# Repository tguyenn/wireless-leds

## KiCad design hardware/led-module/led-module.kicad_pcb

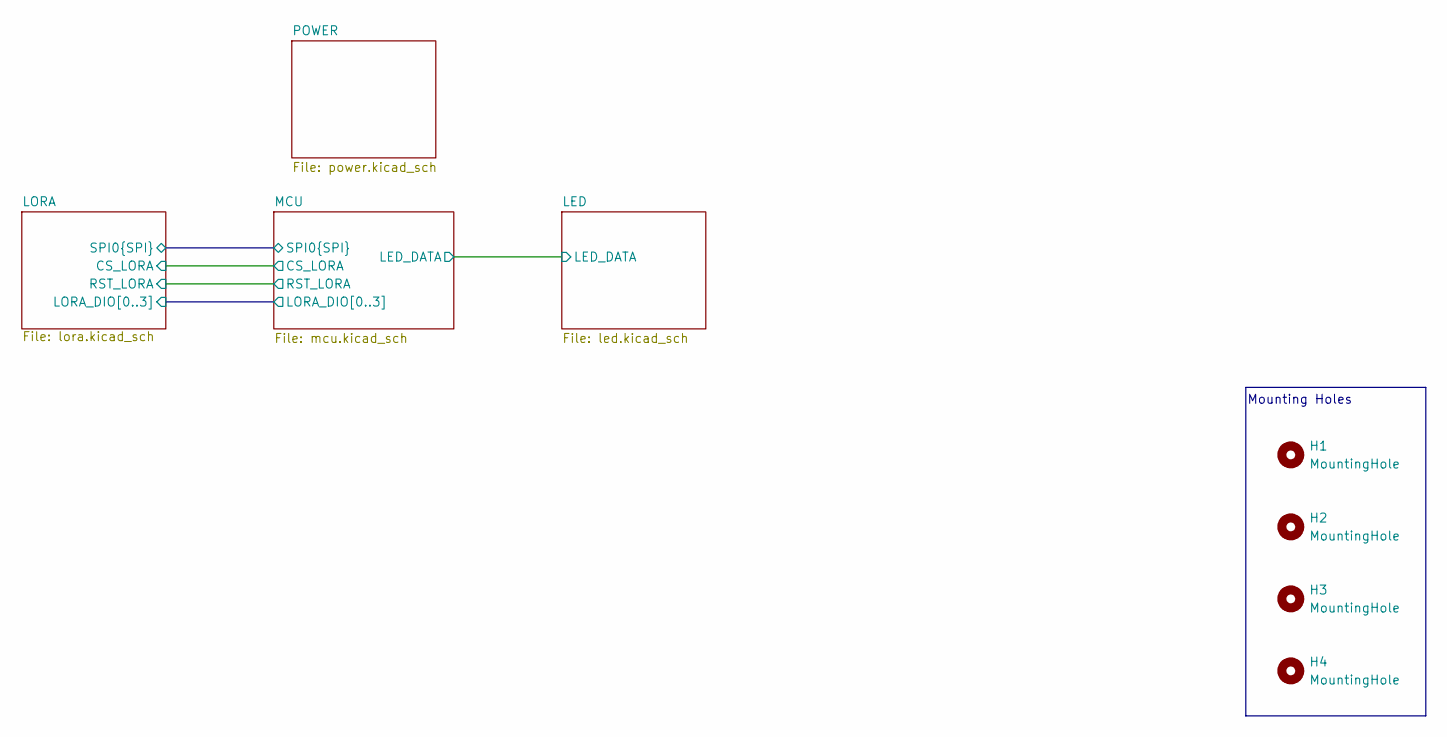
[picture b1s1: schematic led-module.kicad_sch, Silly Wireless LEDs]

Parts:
H1, H2, H3, H4: MountingHole; MountingHole_3mm

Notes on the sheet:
Mounting Holes

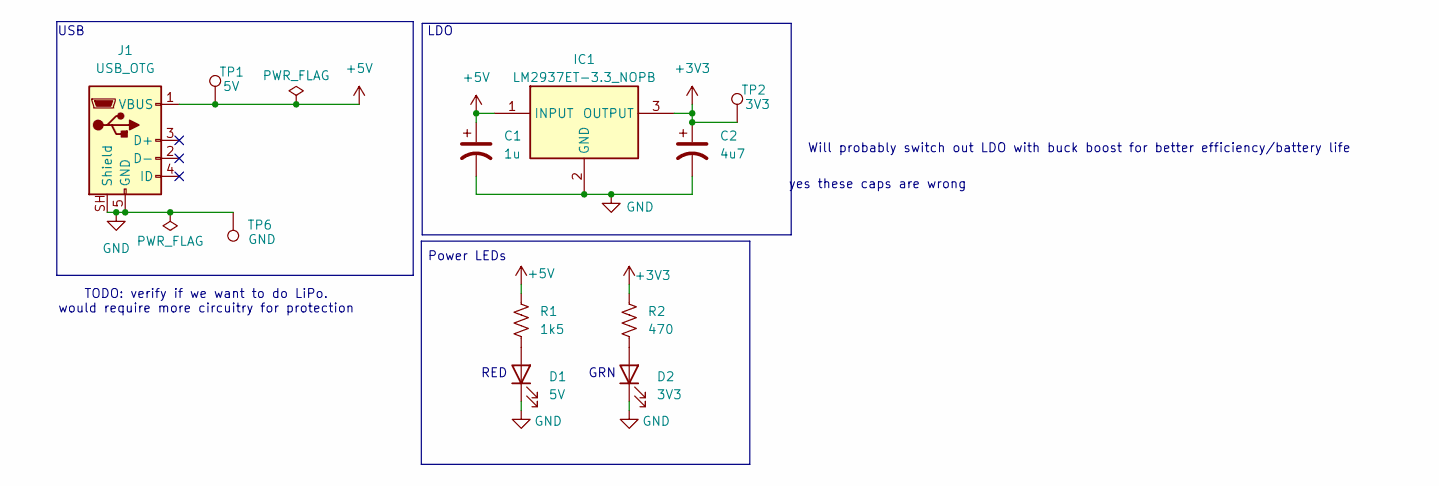
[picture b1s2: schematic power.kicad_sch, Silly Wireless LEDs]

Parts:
C1: 1u; C_0805_2012Metric
C2: 4u7; C_0805_2012Metric
D1: 5V; fuckassled
D2: 3V3; fuckassled
IC1: LM2937ET-3.3_NOPB; TO254P470X1028X1955-3P; Mouser Part Number 926-LM2937ET-3.3NOPB
J1: USB_OTG; USB_Micro-B_GCT_USB3076-30-A
R1: 1k5; R_0805_2012Metric
R2: 470; R_0805_2012Metric
TP1: 5V; bettertestpoint2
TP2: 3V3; bettertestpoint2
TP6: GND; bettertestpoint2

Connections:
+3V3: C2.1, IC1.3 (OUTPUT), R2.1, TP2.1 (1_1); also elsewhere on the board
+5V: C1.1, IC1.1 (INPUT), J1.1 (VBUS), R1.1, TP1.1 (1_1); also elsewhere on the board
GND: C1.2, C2.2, D1.1 (K), D2.1 (K), IC1.2 (GND), J1.5 (GND), J1.SH (Shield), TP6.1 (1_1); also elsewhere on the board
unnamed: D1.2 (A), R1.2
unnamed: D2.2 (A), R2.2

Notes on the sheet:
USB
LDO
GRN
RED
Power LEDs
TODO: verify if we want to do LiPo. would require more circuitry for protection
Will probably switch out LDO with buck boost for better efficiency/battery life
yes these caps are wrong

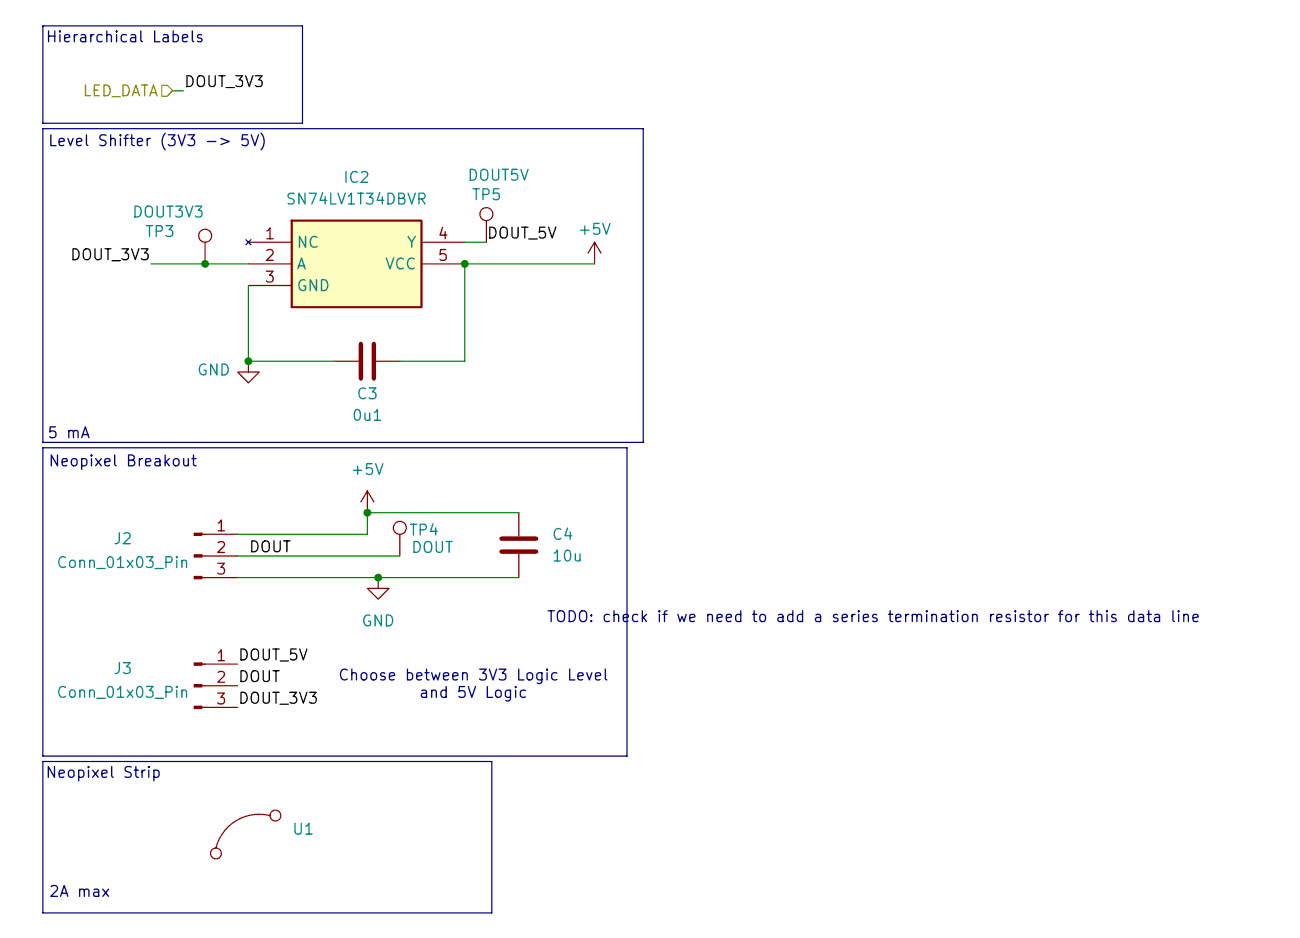
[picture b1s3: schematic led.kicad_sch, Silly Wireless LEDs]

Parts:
C3: 0u1; C_0805_2012Metric
C4: 10u; C_0805_2012Metric
IC2: SN74LV1T34DBVR; SOT95P280X145-5N; Mouser Part Number 595-SN74LV1T34DBVR
J2: Conn_01x03_Pin; PinHeader_1x03_P2.54mm_Vertical
J3: Conn_01x03_Pin; SolderJumper-3_P1.3mm_Open_RoundedPad1.0x1.5mm
TP3: DOUT3V3; bettertestpoint2
TP4: DOUT; bettertestpoint2
TP5: DOUT5V; bettertestpoint2
U1: (no value)

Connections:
+5V: C3.2, C4.1, IC2.5 (VCC), J2.1; also elsewhere on the board
/LED/DOUT: J2.2, J3.2, TP4.1 (1_1)
/LED/DOUT_3V3: IC2.2 (A), J3.3, TP3.1 (1_1); also elsewhere on the board
/LED/DOUT_5V: IC2.4 (Y), J3.1, TP5.1 (1_1)
GND: C3.1, C4.2, IC2.3 (GND), J2.3; also elsewhere on the board

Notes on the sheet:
Hierarchical Labels
Choose between 3V3 Logic Level and 5V Logic
Level Shifter (3V3 -> 5V)
Neopixel Strip
2A max
5 mA
Neopixel Breakout
TODO: check if we need to add a series termination resistor for this data line

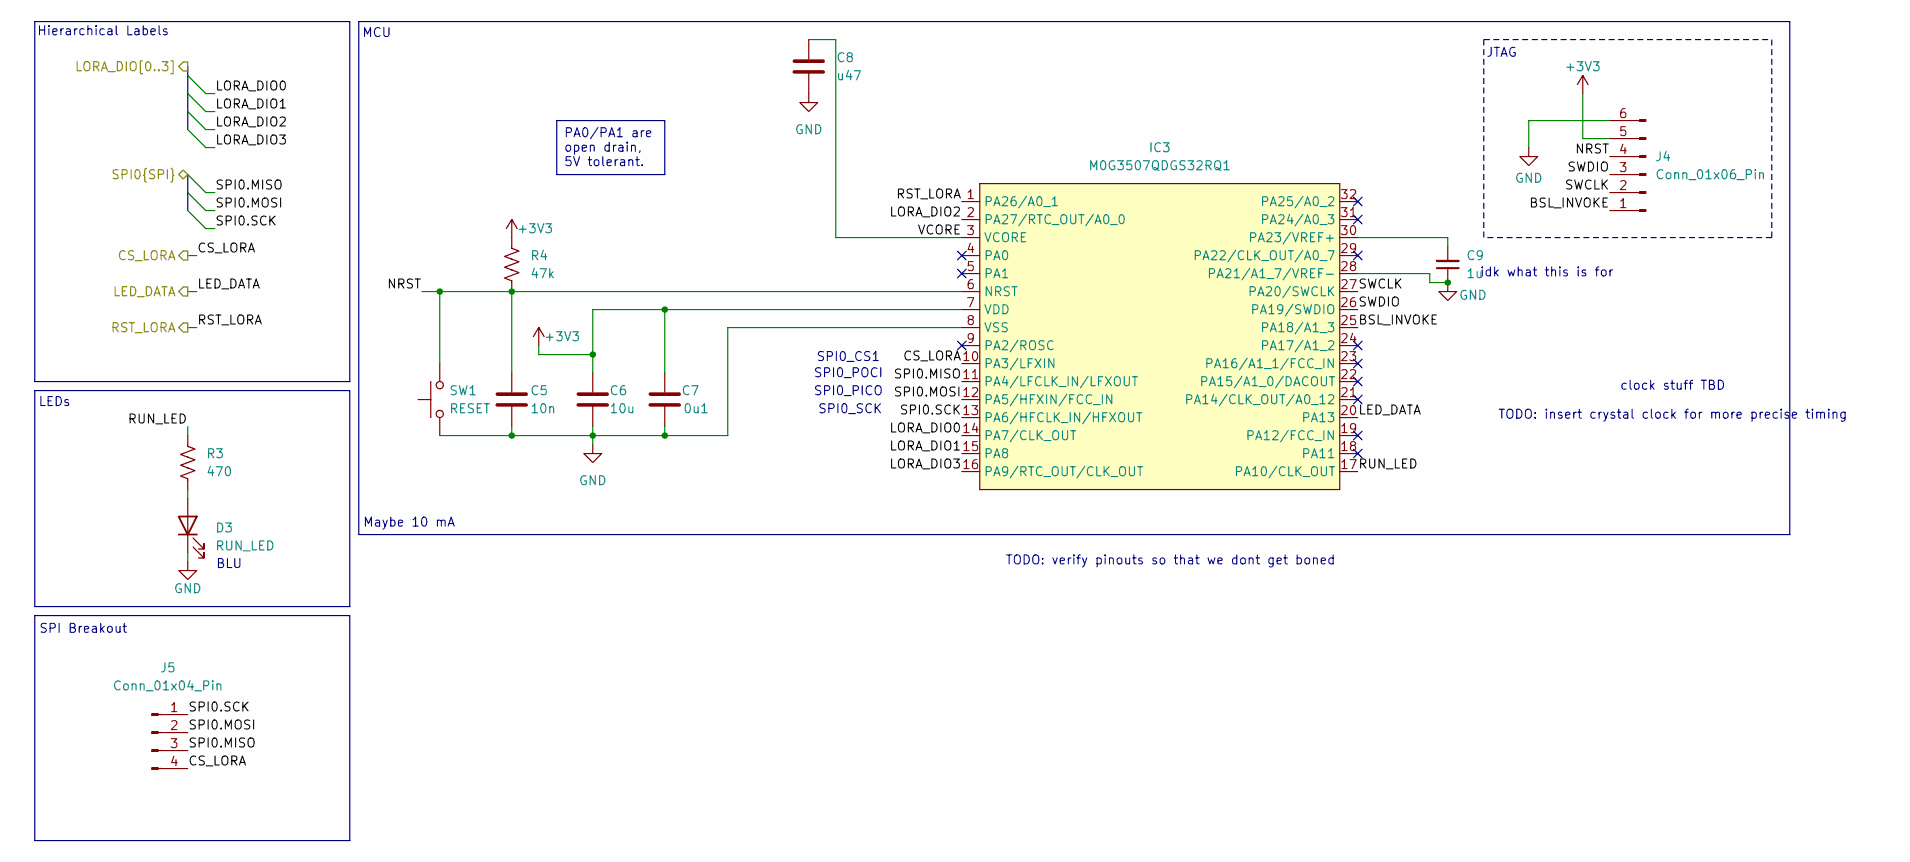
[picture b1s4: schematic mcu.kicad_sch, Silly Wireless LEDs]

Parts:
C5: 10n; C_0805_2012Metric
C6: 10u; C_0805_2012Metric
C7: 0u1; C_0805_2012Metric
C8: u47; C_0805_2012Metric
C9: 1u; C_0805_2012Metric
D3: RUN_LED; fuckassled
IC3: M0G3507QDGS32RQ1; fuckass32pinmsp
J4: Conn_01x06_Pin; PinHeader_1x06_P2.54mm_Vertical
J5: Conn_01x04_Pin; PinHeader_1x04_P2.54mm_Vertical
R3: 470; R_0805_2012Metric
R4: 47k; R_0805_2012Metric
SW1: RESET; SW_PUSH_6mm

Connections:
+3V3: C6.1, C7.1, IC3.7 (VDD), J4.5, R4.1; also elsewhere on the board
/LED/DOUT_3V3: IC3.20 (PA13); also elsewhere on the board
/LORA/CS_LORA: IC3.10 (PA3/LFXIN), J5.4; also elsewhere on the board
/LORA/LORA_DIO0: IC3.14 (PA7/CLK_OUT); also elsewhere on the board
/LORA/LORA_DIO1: IC3.15 (PA8); also elsewhere on the board
/LORA/LORA_DIO2: IC3.2 (PA27/RTC_OUT/A0_0); also elsewhere on the board
/LORA/LORA_DIO3: IC3.16 (PA9/RTC_OUT/CLK_OUT); also elsewhere on the board
/LORA/RST_LORA: IC3.1 (PA26/A0_1); also elsewhere on the board
/LORA/SPI0.MISO: IC3.11 (PA4/LFCLK_IN/LFXOUT), J5.3; also elsewhere on the board
/LORA/SPI0.MOSI: IC3.12 (PA5/HFXIN/FCC_IN), J5.2; also elsewhere on the board
/LORA/SPI0.SCK: IC3.13 (PA6/HFCLK_IN/HFXOUT), J5.1; also elsewhere on the board
/MCU/BSL_INVOKE: IC3.25 (PA18/A1_3), J4.1
/MCU/NRST: C5.1, IC3.6 (NRST), J4.4, R4.2, SW1.2
/MCU/RUN_LED: IC3.17 (PA10/CLK_OUT), R3.1
/MCU/SWCLK: IC3.27 (PA20/SWCLK), J4.2
/MCU/SWDIO: IC3.26 (PA19/SWDIO), J4.3
/MCU/VCORE: C8.1, IC3.3 (VCORE)
GND: C5.2, C6.2, C7.2, C8.2, C9.1, D3.1 (K), IC3.8 (VSS), IC3.28 (PA21/A1_7/VREF-), J4.6, SW1.1; also elsewhere on the board
unnamed: D3.2 (A), R3.2
unnamed: C9.2, IC3.30 (PA23/VREF+)

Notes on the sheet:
Maybe 10 mA
SPI0_PICO
SPI0_CS1
TODO: verify pinouts so that we dont get boned
Hierarchical Labels
SPI0_SCK
idk what this is for
LEDs
SPI0_POCI
JTAG
clock stuff TBD TODO: insert crystal clock for more precise timing
MCU
BLU
SPI Breakout
PA0/PA1 are open drain, 5V tolerant.

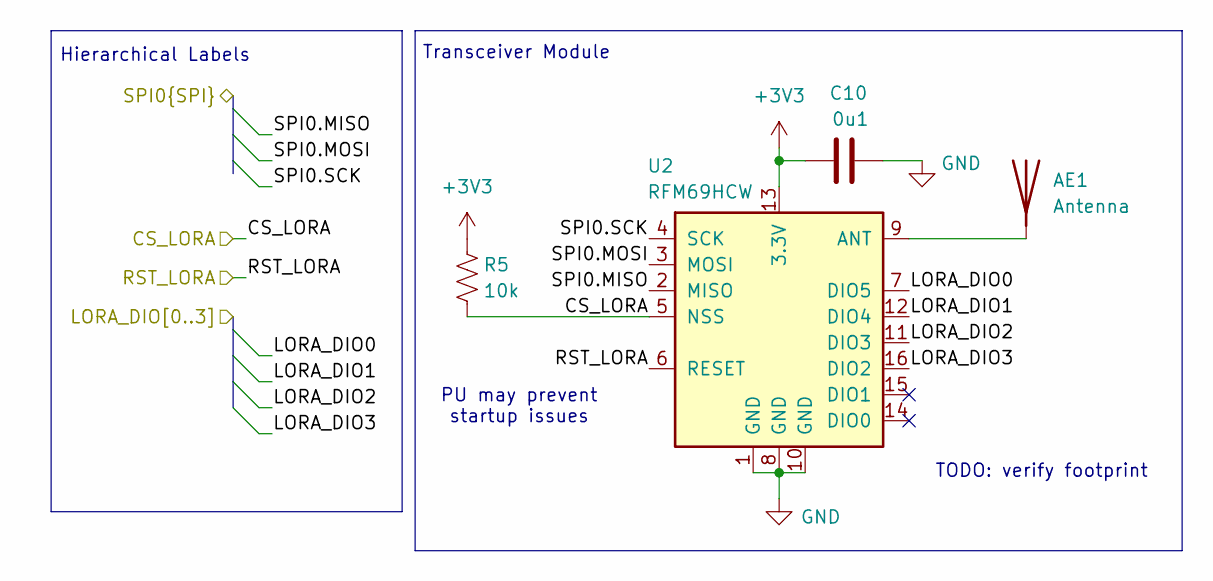
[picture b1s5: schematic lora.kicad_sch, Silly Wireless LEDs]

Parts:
AE1: Antenna; TestPoint_Loop_D1.80mm_Drill1.0mm_Beaded
C10: 0u1; C_0805_2012Metric
R5: 10k; R_0805_2012Metric
U2: RFM69HCW; HOPERF_RFM69HW

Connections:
+3V3: C10.1, R5.2, U2.13 (3.3V); also elsewhere on the board
/LORA/CS_LORA: R5.1, U2.5 (NSS); also elsewhere on the board
/LORA/LORA_DIO0: U2.7 (DIO5); also elsewhere on the board
/LORA/LORA_DIO1: U2.12 (DIO4); also elsewhere on the board
/LORA/LORA_DIO2: U2.11 (DIO3); also elsewhere on the board
/LORA/LORA_DIO3: U2.16 (DIO2); also elsewhere on the board
/LORA/RST_LORA: U2.6 (RESET); also elsewhere on the board
/LORA/SPI0.MISO: U2.2 (MISO); also elsewhere on the board
/LORA/SPI0.MOSI: U2.3 (MOSI); also elsewhere on the board
/LORA/SPI0.SCK: U2.4 (SCK); also elsewhere on the board
GND: C10.2, U2.1 (GND), U2.8 (GND), U2.10 (GND); also elsewhere on the board
unnamed: AE1.1 (A_1), U2.9 (ANT)

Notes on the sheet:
TODO: verify footprint
Hierarchical Labels
Transceiver Module
PU may prevent startup issues

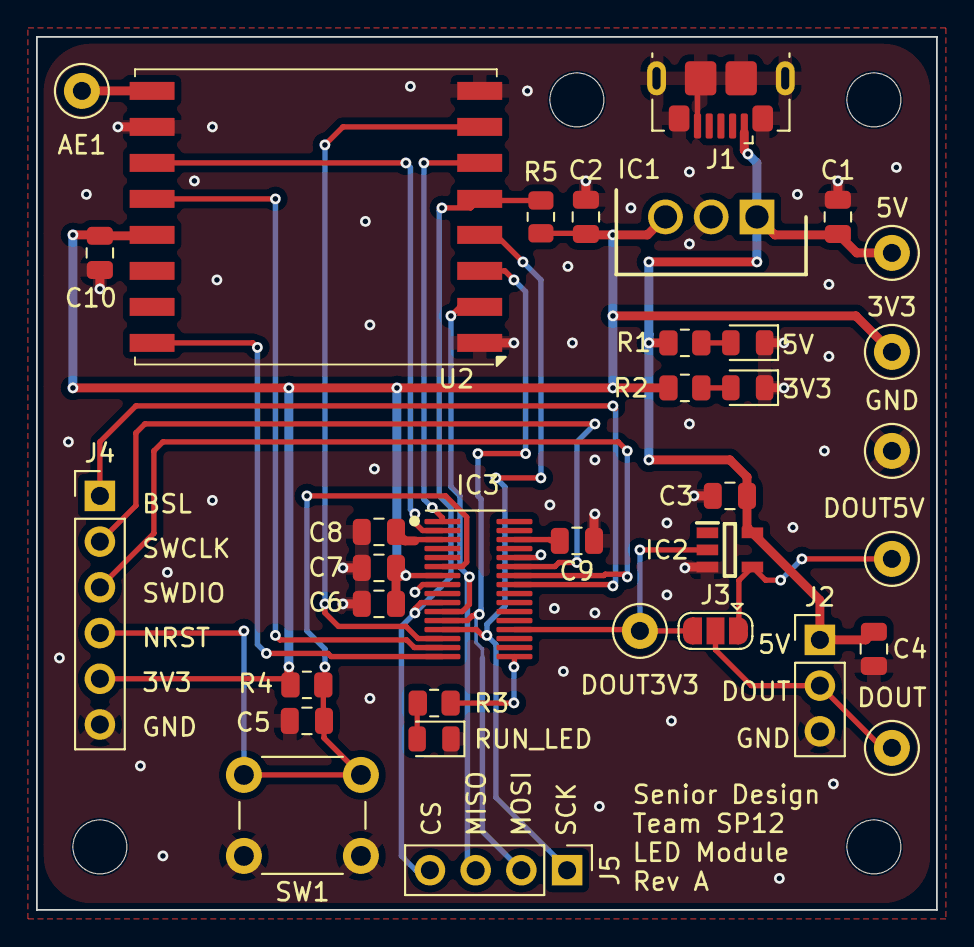
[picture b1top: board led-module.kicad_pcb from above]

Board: 2 copper layers, 50.0 x 48.5 mm, 39 parts (0 on the bottom side), 26 nets.
